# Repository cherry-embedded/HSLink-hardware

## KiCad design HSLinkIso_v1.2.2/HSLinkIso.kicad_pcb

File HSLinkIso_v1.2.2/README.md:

# HSLink-Iso 硬件仓库

## 简述

本仓库是 HSLink-Iso 的 KiCad 硬件开源仓库，请使用 KiCad 9.0 及以上的版本打开

HSLink-Iso 为内置了隔离器的 HSLink-Pro，但是不带隔离电源输出，隔离侧需要使用目标板的电源进行供电，供电范围为 2.5V~5V

## 选型

隔离器选型如下：

- 德州仪器 ISO7741 (已验证，推荐)
- 纳芯微 NSi8241S0D (已验证)
- 川土微 CA-IS3741LB (已验证)

## 软件

HSLink Iso 软件参考<https://github.com/cherry-embedded/CherryDAP>。

## 外壳

HSLink Iso 的 PCB 适配 ulink v2 短体款外壳，请自行在电商平台选购

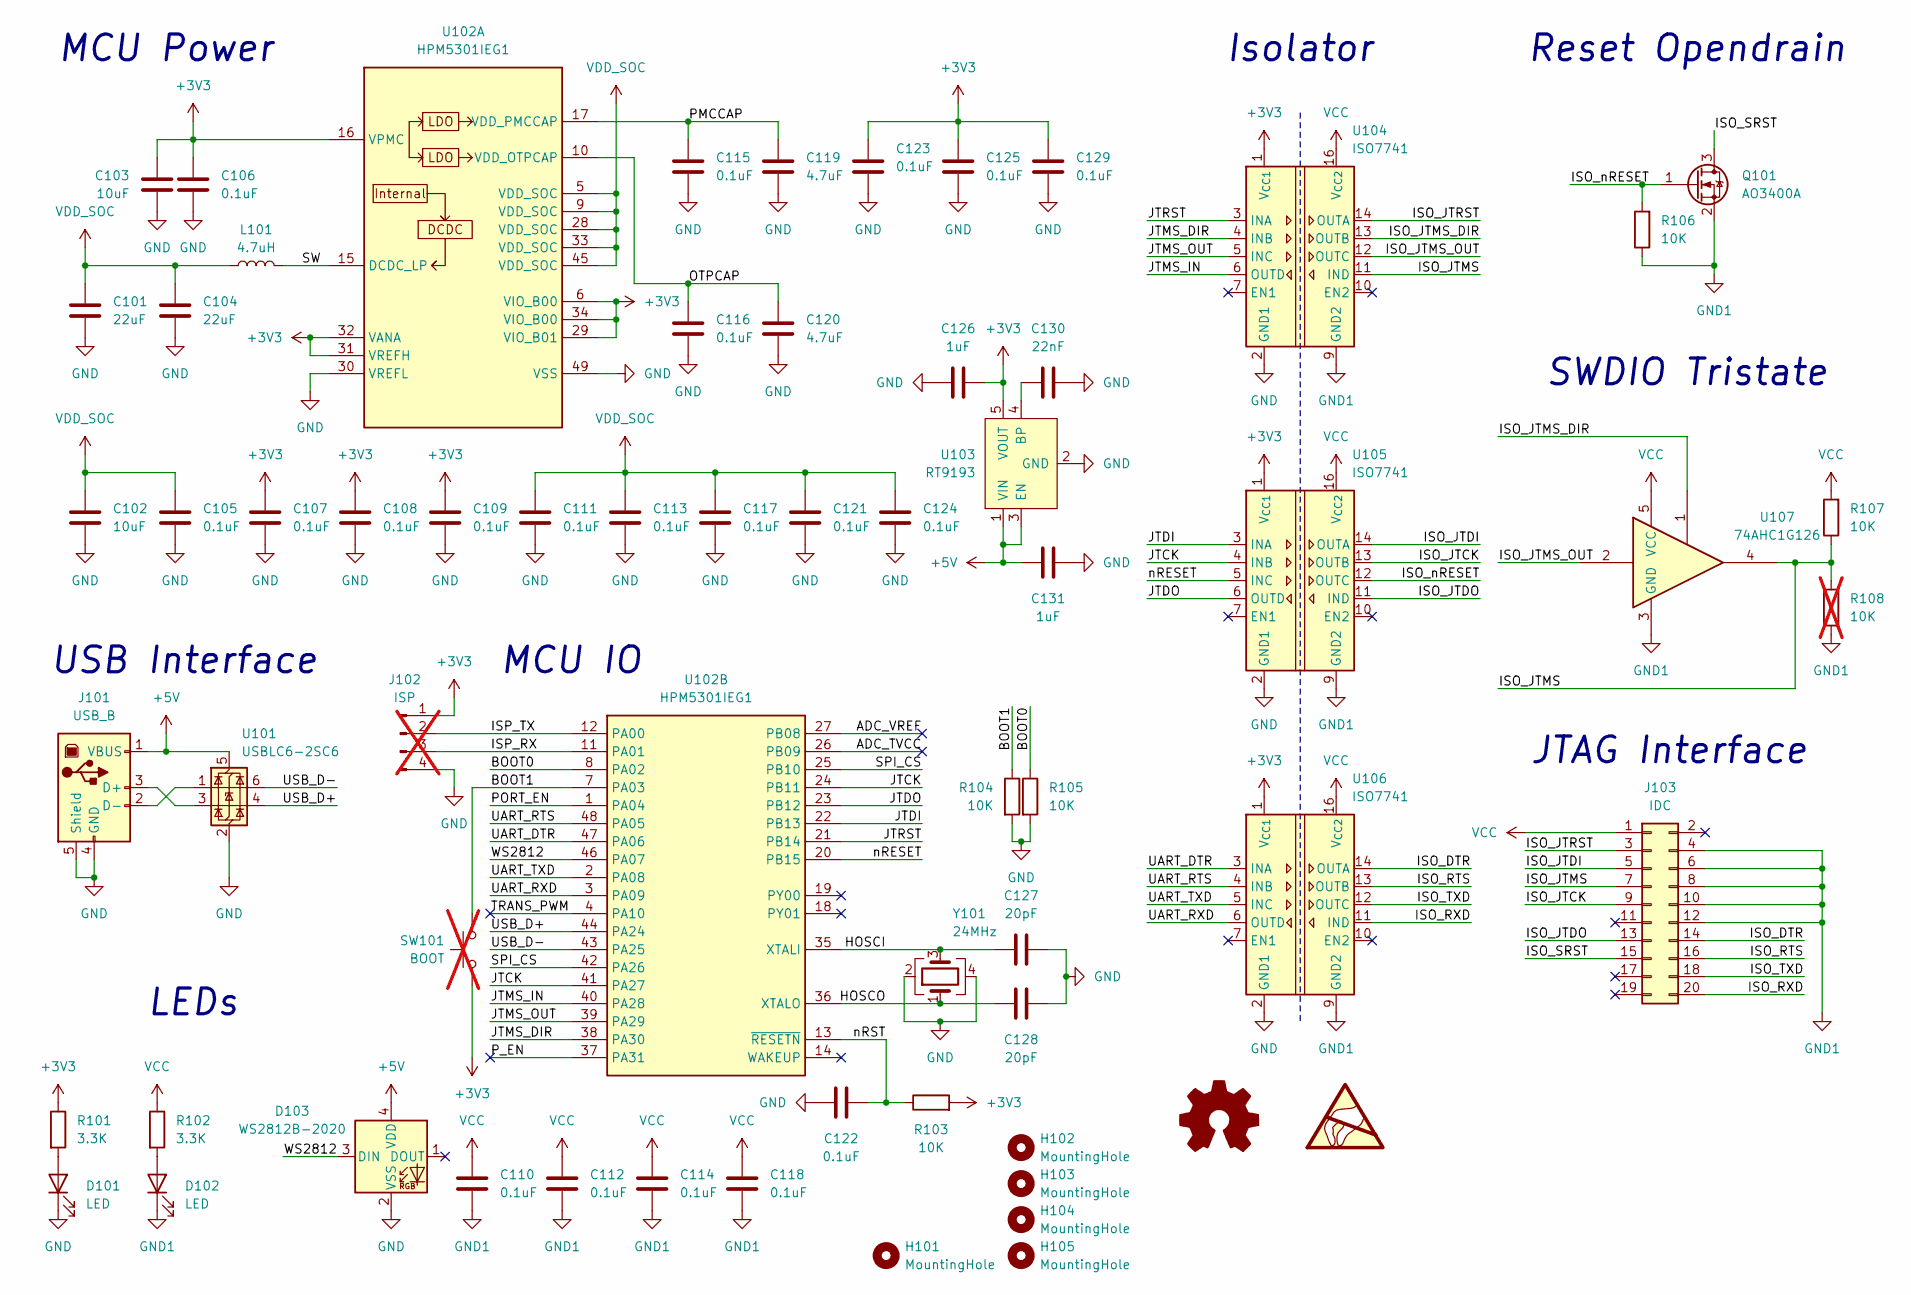
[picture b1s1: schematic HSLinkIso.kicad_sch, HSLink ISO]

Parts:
C101, C104: 22uF; C_0805_2012Metric
C102, C103: 10uF; C_0805_2012Metric
C105, C106, C107, C108, C109, C110, C111, C112, C113, C114, C115, C116, C117, C118, C121, C122, C123, C124, C125, C129: 0.1uF; C_0603_1608Metric
C119, C120: 4.7uF; C_0603_1608Metric
C126, C131: 1uF; C_0603_1608Metric
C127, C128: 20pF; C_0603_1608Metric
C130: 22nF; C_0603_1608Metric
D101, D102: LED; LED_0603_1608Metric
D103: WS2812B-2020; LED_WS2812B-2020_PLCC4_2.0x2.0mm
H101: MountingHole; MountingHole_3.2mm_M3
H102, H103, H104, H105: MountingHole; MountingHole_2.2mm_M2
J101: USB_B; USB_B_Lumberg_2411_02_Horizontal
J102: ISP; PinHeader_1x04_P2.54mm_Vertical; not fitted
J103: IDC; IDC-Header_2x10_P2.54mm_Horizontal
L101: 4.7uH; L_Sunlord_SWPA4020S
Q101: AO3400A; SOT-23
R101, R102: 3.3K; R_0603_1608Metric
R103, R104, R105, R106, R107: 10K; R_0603_1608Metric
R108: 10K; R_0603_1608Metric; not fitted
SW101: BOOT; PinHeader_1x02_P2.54mm_Vertical; not fitted
U101: USBLC6-2SC6; SOT-23-6
U102: HPM5301IEG1; QFN-48-1EP_6x6mm_P0.4mm_EP4.2x4.2mm
U103: RT9193; SOT-23-5
U104, U105, U106: ISO7741; QSOP-16_3.9x4.9mm_P0.635mm
U107: 74AHC1G126; SOT-23-5
Y101: 24MHz; Crystal_SMD_3225-4Pin_3.2x2.5mm

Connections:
+3V3: C103.1, C106.1, C107.1, C108.1, C109.1, C123.1, C125.1, C126.1, C129.1, J102.1, R101.1, R103.2, SW101.2, U102.6 (VIO_B00), U102.16 (VPMC), U102.29 (VIO_B01), U102.31 (VREFH), U102.32 (VANA), U102.34 (VIO_B00), U103.5 (VOUT), U104.1 (V_{CC1}), U105.1 (V_{CC1}), U106.1 (V_{CC1})
+5V: C131.1, D103.4 (VDD), J101.1 (VBUS), U101.5 (VBUS), U103.1 (VIN), U103.3 (EN)
/ADC_TVCC: U102.26 (PB09)
/ADC_VREF: U102.27 (PB08)
/BOOT0: R105.1, U102.8 (PA02)
/BOOT1: R104.1, SW101.1, U102.7 (PA03)
/HOSCI: C127.1, U102.35 (XTALI), Y101.3
/HOSCO: C128.1, U102.36 (XTALO), Y101.1
/ISO_DTR: J103.14, U106.14 (OUTA)
/ISO_JTCK: J103.9, U105.13 (OUTB)
/ISO_JTDI: J103.5, U105.14 (OUTA)
/ISO_JTDO: J103.13, U105.11 (IND)
/ISO_JTMS: J103.7, R107.1, R108.2, U104.11 (IND), U107.4
/ISO_JTMS_DIR: U104.13 (OUTB), U107.1
/ISO_JTMS_OUT: U104.12 (OUTC), U107.2
/ISO_JTRST: J103.3, U104.14 (OUTA)
/ISO_RTS: J103.16, U106.13 (OUTB)
/ISO_RXD: J103.20, U106.11 (IND)
/ISO_SRST: J103.15, Q101.3 (D)
/ISO_TXD: J103.18, U106.12 (OUTC)
/ISO_nRESET: Q101.1 (G), R106.2, U105.12 (OUTC)
/ISP_RX: J102.3, U102.11 (PA01)
/ISP_TX: J102.2, U102.12 (PA00)
/JTCK: U102.24 (PB11), U102.41 (PA27), U105.4 (INB)
/JTDI: U102.22 (PB13), U105.3 (INA)
/JTDO: U102.23 (PB12), U105.6 (OUTD)
/JTMS_DIR: U102.38 (PA30), U104.4 (INB)
/JTMS_IN: U102.40 (PA28), U104.6 (OUTD)
/JTMS_OUT: U102.39 (PA29), U104.5 (INC)
/JTRST: U102.21 (PB14), U104.3 (INA)
/OTPCAP: C116.1, C120.1, U102.10 (VDD_OTPCAP)
/PMCCAP: C115.1, C119.1, U102.17 (VDD_PMCCAP)
/PORT_EN: U102.1 (PA04)
/P_EN: U102.37 (PA31)
/SPI_CS: U102.25 (PB10), U102.42 (PA26)
/SW: L101.2, U102.15 (DCDC_LP)
/TRANS_PWM: U102.4 (PA10)
/UART_DTR: U102.47 (PA06), U106.3 (INA)
/UART_RTS: U102.48 (PA05), U106.4 (INB)
/UART_RXD: U102.3 (PA09), U106.6 (OUTD)
/UART_TXD: U102.2 (PA08), U106.5 (INC)
/USB_D+: U101.4 (I/O2), U102.44 (PA24)
/USB_D-: U101.6 (I/O1), U102.43 (PA25)
/WS2812: D103.3 (DIN), U102.46 (PA07)
/nRESET: U102.20 (PB15), U105.5 (INC)
/nRST: C122.1, R103.1, U102.13 (~RESETN)
GND: C101.2, C102.2, C103.2, C104.2, C105.2, C106.2, C107.2, C108.2, C109.2, C111.2, C113.2, C115.2, C116.2, C117.2, C119.2, C120.2, C121.2, C122.2, C123.2, C124.2, C125.2, C126.2, C127.2, C128.2, C129.2, C130.2, C131.2, D101.1 (K), D103.2 (VSS), J101.4 (GND), J101.5 (Shield), J102.4, R104.2, R105.2, U101.2 (GND), U102.30 (VREFL), U102.49 (VSS), U103.2 (GND), U104.2 (GND1), U104.8 (GND1), U105.2 (GND1), U105.8 (GND1), U106.2 (GND1), U106.8 (GND1), Y101.2, Y101.4
GND1: C110.2, C112.2, C114.2, C118.2, D102.1 (K), J103.4, J103.6, J103.8, J103.10, J103.12, Q101.2 (S), R106.1, R108.1, U104.9 (GND2), U104.15 (GND2), U105.9 (GND2), U105.15 (GND2), U106.9 (GND2), U106.15 (GND2), U107.3 (GND)
unnamed: D101.2 (A), R101.2
unnamed: D102.2 (A), R102.2
unnamed: J101.3 (D+), U101.3 (I/O2)
unnamed: J101.2 (D-), U101.1 (I/O1)
unnamed: C130.1, U103.4 (BP)
VCC: C110.1, C112.1, C114.1, C118.1, J103.1, R102.1, R107.2, U104.16 (V_{CC2}), U105.16 (V_{CC2}), U106.16 (V_{CC2}), U107.5 (VCC)
VDD_SOC: C101.1, C102.1, C104.1, C105.1, C111.1, C113.1, C117.1, C121.1, C124.1, L101.1, U102.5 (VDD_SOC), U102.9 (VDD_SOC), U102.28 (VDD_SOC), U102.33 (VDD_SOC), U102.45 (VDD_SOC)

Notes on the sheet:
JTAG Interface
Isolator
USB Interface
Reset Opendrain
MCU Power
MCU IO
SWDIO Tristate
LEDs

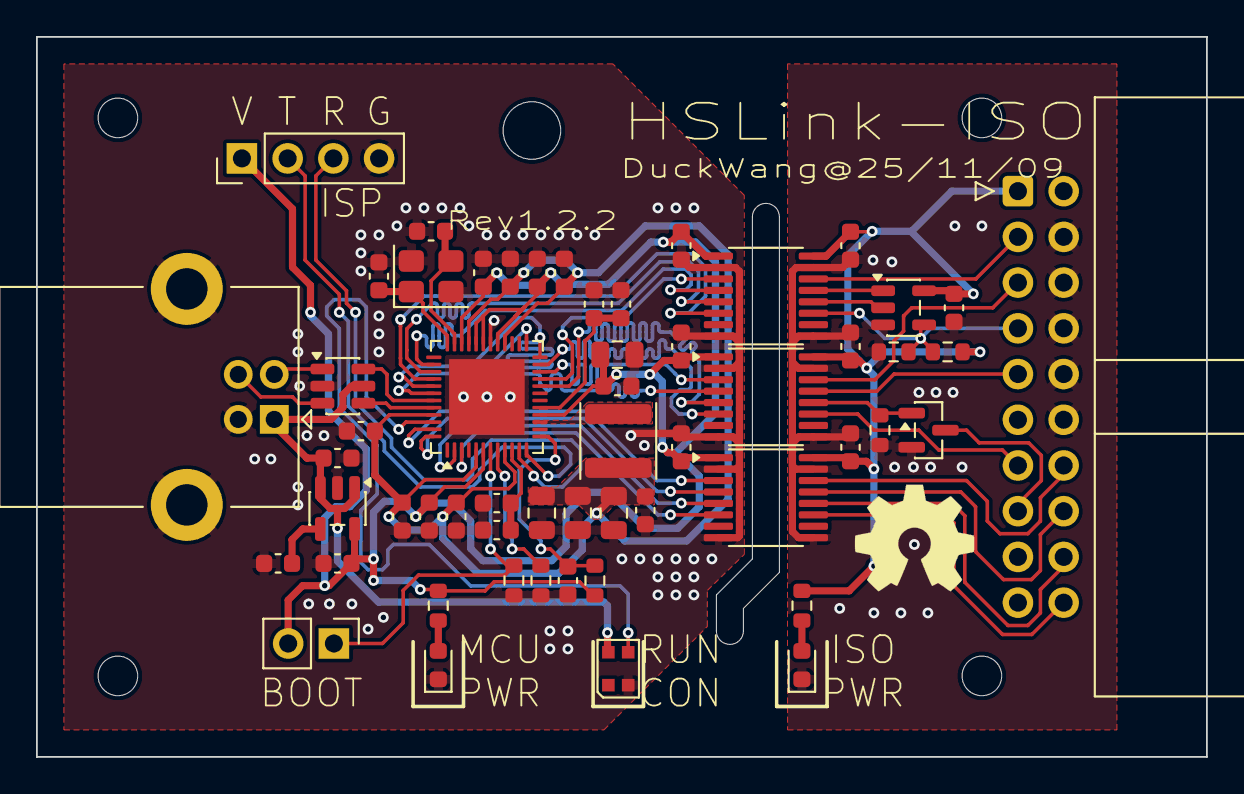
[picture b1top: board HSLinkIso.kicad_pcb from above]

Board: 2 copper layers, 65.0 x 40.0 mm, 61 parts (0 on the bottom side), 50 nets.

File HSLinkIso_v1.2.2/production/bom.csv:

Designator,Footprint,Quantity,Value,LCSC Part #
"C101, C104",0805,2,22uF,
"C102, C103",0805,2,10uF,
"C105, C106, C107, C108, C109, C110, C111, C112, C113, C114, C115, C116, C117, C118, C121, C122, C123, C124, C125, C129",0603,20,0.1uF,
"C119, C120",0603,2,4.7uF,
"C126, C131",0603,2,1uF,
"C127, C128",0603,2,20pF,
C130,0603,1,22nF,
"D101, D102",0603,2,LED,
D103,LED_WS2812B-2020_PLCC4_2.0x2.0mm,1,WS2812B-2020,
J101,USB_B_Lumberg_2411_02_Horizontal,1,USB_B,
J103,IDC-Header_2x10_P2.54mm_Horizontal,1,IDC,
L101,L_Sunlord_SWPA4020S,1,4.7uH,
Q101,SOT-23,1,AO3400A,
"R101, R102",0603,2,3.3K,
"R103, R104, R105, R106, R107",0603,5,10K,
U101,SOT-23-6,1,USBLC6-2SC6,
U102,QFN-48-1EP_6x6mm_P0.4mm_EP4.2x4.2mm,1,HPM5301IEG1,
U103,SOT-23-5,1,RT9193,
"U104, U105, U106",QSOP-16_3.9x4.9mm_P0.635mm,3,ISO7741,
U107,SOT-23-5,1,74AHC1G126,
Y101,Crystal_SMD_3225-4Pin_3.2x2.5mm,1,24MHz,

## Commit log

2025-12-05 add: HSLinkIso hardware v1.2.2
